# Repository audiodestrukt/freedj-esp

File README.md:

# freedj-esp

DJ decks on ESP32 (formerly esp32-mediaplayer). Two firmwares live here:

- **The ESP32-P4 deck** in [`p4/deck`](p4/deck/README.md): a small CDJ/XDJ-style player
  with Pro DJ Link sync, rekordbox analysis, a touch screen and a 3D-printed enclosure design.
- **The ESP32-A1S timecode-vinyl player** (this directory): described below.

The A1S firmware is an ESP32-A1S media player aimed at eventually driving a portable DJ turntable
with Serato timecode vinyl control. Plays MP3/WAV from an SD card with
variable-speed playback (pitched or pitch-preserving), OLED file browser, and
cue points.

The P4 deck shares the deck events, DJ2Go decoder and WSOLA with this firmware.

The long-term target is a self-contained turntable deck: drop a control
record on the platter and the ESP32 decodes position and speed from the
timecode, playing the selected MP3 in perfect sync with the vinyl.

## Status

Scaffold-complete. Untested on hardware — awaiting a board.

| Area | State |
| --- | --- |
| PlatformIO project (ES8388 + AC101 build envs) | Done |
| MP3 + WAV playback from SD | Done |
| SSD1306 OLED browser + now-playing UI | Done |
| Rotary encoder + 3 buttons, long-press state machine | Done |
| Pitched variable speed (resampler) | Done |
| Keylock variable speed (WSOLA) | Done (host-validated via SDL player) |
| Cue points (byte-level seek) | Done (glitches on MP3 mid-frame) |
| Timecode: speed + direction | Done (validated on Serato CD) |
| Timecode: bit decode + absolute position | Done host-side; ESP32 LUT pending |
| Codec RX (line-in) path for timecode input | TODO |
| Host simulation (SDL GUI + DSP harnesses) | Done |

## Hardware

- **Board:** AI-Thinker ESP32-A1S Audio Kit. Two revisions ship with
  different codecs (ES8388 or AC101) with no PCB silkscreen difference —
  check the IC marking near the 3.5 mm jacks. Both are supported by
  separate PlatformIO environments.
- **SD card:** inserted in the A1S slot (uses SD-MMC 1-bit mode).
- **Display:** 128×64 SSD1306 OLED over I²C. Shares the codec's I²C bus
  (SDA = GPIO 33, SCL = GPIO 32). No conflict: SSD1306 lives at `0x3C`,
  ES8388 at `0x10`, AC101 at `0x1A`.
- **Input:** 1 rotary encoder with push switch + 3 push buttons.
  Internal pull-ups are used; wire buttons to GND.

### Pin assignments

Default pin mapping (see `include/config.h` to adjust):

| Function | GPIO |
| --- | --- |
| Encoder A | 19 |
| Encoder B | 23 |
| Encoder switch | 18 |
| Button: Play/Pause | 5 |
| Button: Back | 21 |
| Button: Cue | 22 |
| OLED SDA (shared with codec) | 33 |
| OLED SCL (shared with codec) | 32 |

These are all pins exposed on the A1S J1/J2 expansion headers. The codec,
I²S bus, and SD card use their own dedicated pins and should be left alone.

## Building

Install [PlatformIO](https://platformio.org/) (CLI or the VS Code
extension). Then pick the build environment that matches your A1S codec:

```bash
# ES8388 variant (more common on recent A1S boards)
pio run -e esp32-a1s-es8388 -t upload

# AC101 variant
pio run -e esp32-a1s-ac101 -t upload
```

Serial monitor:

```bash
pio device monitor -b 115200
```

Wrong environment? Audio will be silent or distorted even though the board
boots — re-flash with the other env.

## Controls

| Screen | Input | Action |
| --- | --- | --- |
| Browser | Encoder CW/CCW | Scroll file list |
| Browser | Encoder press / Play | Play selected file |
| Playing | Encoder CW/CCW | Nudge speed ±0.02× |
| Playing | Encoder short-press | Snap speed to 1.0× |
| Playing | Encoder long-press (400 ms) | Toggle keylock / pitched |
| Playing | Play | Pause / resume |
| Playing | Back | Stop and return to browser |
| Playing | Cue short-press | Jump to cue point (or restart if no cue) |
| Playing | Cue long-press | Set cue point at current position |

### Serial interface

For bringing up an A1S without an OLED wired: the firmware mirrors the
UI to the 115200-baud serial console and accepts single-char keys.
`pio device monitor -b 115200`, then:

| Screen | Key | Action |
| --- | --- | --- |
| Browser | `w` / `s` | Scroll up / down |
| Browser | Enter | Play selected |
| Playing | `+` / `-` | Nudge speed ±0.02× |
| Playing | `[` / `]` | Nudge speed ±0.10× (coarse) |
| Playing | `=` | Snap speed to 1.0× |
| Playing | `K` | Toggle keylock / pitched |
| Playing | `p` or space | Pause / resume |
| Playing | `b` | Back to browser |
| Playing | `c` | Jump to cue |
| Playing | `C` | Set cue at current position |
| Any | `t` | Arm / disarm timecode input |
| Any | `?` | Print key help |

## How it works

### Audio pipeline

```
SD file ─► StreamCopy ─► EncodedAudioStream(MP3 or WAV)
                                    │
                                    ▼
                         ┌──── ResampleStream ────┐    (Pitched mode)
                         │                        │
                         └──── WsolaStream   ─────┘    (Keylock mode)
                                    │
                                    ▼
                           AudioBoardStream (I²S + codec)
```

The player wires both speed stages in parallel and routes the copier
to whichever matches the selected mode. Only the active stage drains input.

### WSOLA (Waveform-Similarity Overlap-Add)

Time-domain pitch-preserving stretching. For each output chunk:

1. Extract a 1024-sample analysis window from the input, starting near
   `analysisPos += HOP_SYN × speed`.
2. Search ±128 samples around that position for the window whose leading
   samples best match the natural continuation of the previous window
   (AMDF similarity on mono-summed input — cheaper than cross-correlation).
3. Hann-window the chosen frame and overlap-add onto the running output
   (75 % overlap).

Parameters (44.1 kHz): `FRAME_N = 1024`, `HOP_SYN = 256`, `SEARCH = 128`.
See `src/wsola.cpp`.

### CPU budget (unmeasured)

Rough estimates on a 240 MHz ESP32, everything running on core 1
(Arduino's main loop); core 0 is idle since we don't use WiFi/BT.

| Path                  | Est. one-core utilization |
| --------------------- | ------------------------- |
| Pitched mode          | ~20–30% (MP3 decode + DMA I²S) |
| Keylock mode          | ~35–50% (+ WSOLA: AMDF search dominates) |
| Timecode armed        | small — ZC + LFSR, a few % |

WSOLA's cost is dominated by the AMDF search: `FRAME_N × 2·SEARCH`
abs-diffs per `HOP_SYN` output samples on a mono-summed input, roughly
1K ops per output sample. Not measured on hardware yet — wrap a probe
around `player::loopTick()` with `esp_timer_get_time()` when we want a
real number.

### Timecode decoder

Implements Serato Control Vinyl and Serato Control CD decoding — speed,
direction, and absolute position on the record/CD. Source:
`src/timecode.{h,cpp}`.

```
int16 stereo in ─► per-channel ZC with hysteresis + DC-tracking zero
                   │                              │
                   ▼                              ▼
           direction (primary vs          period between primary ZCs
            secondary polarity at ZC)     → carrier speed (EMA-smoothed)
                   │                              │
                   ▼                              │
         bit sample at secondary ZC               │
         (|primary| vs running ref_level → 1/0)   │
                   │                              │
                   ▼                              │
         20-bit shift register + LFSR predictor   │
         (VALID_BITS = 24 consecutive matches     │
          before position is trusted)             │
                   │                              │
                   ▼                              │
         LUT lookup ► absolute cycle position ◄───┘
```

**Supported formats** (constants are published reverse-engineered facts
about Serato's commercial products):

| Format | Carrier | Bits | Seed | Taps | Length |
| --- | --- | --- | --- | --- | --- |
| Serato Control Vinyl 2nd ed. | 1 kHz | 20 | `0x59017` | `0x361e4` | 712 000 cycles |
| Serato Control CD | 1 kHz | 20 | `0xd8b40` | `0x34d54` | 950 000 cycles |

Resolution is one decoded cycle per millisecond of reference playback
(1 kHz carrier). With `VALID_BITS = 24`, lock takes ~25 ms of correct
bits plus ref-level EMA settling — measured at ~160 ms cold-start on a
clean capture.

**Host validation.** A reference 980 s capture of the Serato CD in the
repo (`timecode.wav`, not committed — supply your own) is decoded by
`native/timecode_analyze`; seek-offset positions decode linearly across
the usable range of the disc with perfect inter-sample consistency. A
constant LFSR-to-disc offset (≈2604 cycles for this pressing) is
absorbed when the player anchors position at playback start.

**ESP32 caveat.** The position LUT is host-only today —
`std::unordered_map` with ~30 MB footprint for `serato_cd`. The ESP32
path returns `position() = -1` while still producing correct speed and
direction. A PSRAM-resident compact LUT is the remaining work to ship
position decode on hardware.

**Licensing.** This is a clean-room implementation of the algorithm
described by [xwax](https://xwax.org/) — no xwax source was copied.
xwax is GPL-3; its code cannot be merged into this project without
relicensing. The format constants above are facts about Serato's
products, not copyrightable expression, and appear in multiple
independent open-source DVS implementations.

## Host simulation and testing

The firmware is structured so the DSP modules (`src/wsola.{h,cpp}` and
`src/timecode.{h,cpp}`) build cleanly against a host toolchain via
`-DWSOLA_NATIVE -DTIMECODE_NATIVE`, letting us validate them without
hardware. Host artifacts live under `native/` (SDL + gcc) and `sim/`
(Wokwi headless simulation).

### native/ — gcc + SDL harnesses

```
make -C native            # builds everything
```

Produces four binaries:

| Binary | Purpose |
| --- | --- |
| `wsola_play <file.wav> [speed]` | Feed a WAV through `Wsola`, emit raw PCM to stdout. Pipe to `aplay -f S16_LE -c 2 -r 44100`. |
| `mediaplayer ./media` | SDL 640×360 window reproducing the ESP32 UI (browser + playing screen) against a real WAV directory. Keyboard stands in for encoder/buttons. |
| `timecode_test` | Synthetic stereo-carrier smoke test — exercises ZC, direction, and period estimation across 500/1000/1500/2000 Hz. |
| `timecode_analyze <file.wav> [hop_ms]` | Stream mode: print speed/locked/position time series. |
| `timecode_analyze <file.wav> seek <off_s> [dur_s]` | Seek mode: decode a window, compare decoded position to ground-truth cycle offset. |
| `vinyl_demo <tc.wav> <music.wav> <tc_speed>` | End-to-end loop: resamples TC at `tc_speed` (simulating platter spin), decodes it, drives WSOLA on the music — music plays keylocked at the decoded speed. Stereo PCM to stdout. |

The same `src/wsola.cpp` and `src/timecode.cpp` that ship to the ESP32
are compiled here — only Arduino and AudioTools includes are guarded
out. One source of truth for DSP correctness.

### sim/ — Wokwi headless simulation

`sim/diagram.json` + `sim/wokwi.toml` + `sim/scenario.test.yaml` drive
the Wokwi CLI against the `esp32-sim` PlatformIO environment
(`src/main_sim.cpp` replaces `main.cpp`, strips audio deps, keeps UI +
controls). Serial assertions verify the state machine.

```
make -C native run_wokwi    # builds esp32-sim firmware and runs scenario
```

Needs `WOKWI_CLI_TOKEN` in `./.env` (gitignored); the target bails with
a clear error if it's missing.

This validates the non-audio half of the firmware (OLED rendering,
encoder/button handling, state transitions). Wokwi does **not**
simulate the ESP32 I²S peripheral — `mediaplayer` in `native/` is where
audio behaviour is exercised.

Common run targets (all under `make -C native`):

| Target | What it does |
| --- | --- |
| `run_sim` | Launch the SDL mediaplayer against `native/media/` |
| `run_wokwi` | Build esp32-sim firmware and run the Wokwi scenario |
| `run_play WAV=x.wav SPEED=1.25` | Pipe `wsola_play` output to `aplay` |
| `run_tc` | Run the synthetic-carrier timecode smoke test |
| `run_tc_wav TC_WAV=path.wav` | Stream a real capture through `timecode_analyze` |
| `run_vinyl_demo DEMO_SPEED=1.25 MUSIC=path.wav` | TC drives music playback (keylocked) via WSOLA — piped to aplay |

## References / inspiration

- [pschatzmann/arduino-audio-tools](https://github.com/pschatzmann/arduino-audio-tools) —
  the audio framework this player is built on, especially the
  [`player-sd-audiokit`](https://github.com/pschatzmann/arduino-audio-tools/tree/main/examples/examples-player/player-sd-audiokit) example.
- [bbulkow/loudframe](https://github.com/bbulkow/loudframe) — reference for
  SD playback and variable-speed handling on the A1S.
- [xwax](https://xwax.org/) — algorithmic reference for the timecode
  decoder. Our implementation is a clean-room rewrite (GPL-3 xwax code
  is not included); the Serato format constants are reverse-engineered
  facts originally published there.
- Verhelst & Roelands, "An Overlap-Add Technique Based on Waveform
  Similarity (WSOLA) For High Quality Time-Scale Modification of Speech",
  ICASSP 1993.

## License

Copyright (c) 2026 Dan Newcome.

- **Software** (both firmwares, the simulator, tests and tools): [GPL-3.0-or-later](LICENSE).
- **Hardware** (`p4/deck/hardware`: enclosure CAD, generated STLs, renders): [CERN-OHL-S-2.0](p4/deck/hardware/LICENSE).

- **Names:** "freedj" and audiodestrukt are Dan Newcome's trademarks and aren't covered by those licences. If you ship a modified version, give it a name of your own.
- **No affiliation:** not affiliated with or endorsed by Pioneer DJ / AlphaTheta, Serato, Numark or any other brand named here. Those names are used only to describe compatibility.

See [COPYRIGHT.md](COPYRIGHT.md) for which licence covers what, the third-party code, and trademarks.

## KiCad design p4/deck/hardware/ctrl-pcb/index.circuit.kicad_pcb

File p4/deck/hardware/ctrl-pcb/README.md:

# freedj control board

One 42 × 58 mm two-layer board under CUE / PLAY. It carries:
- the two buttons and their ring LEDs,
- the pitch fader input,
- one I2C target chip that does the ADC, button debouncing and LEDs for the host.

The AS5600 jog encoder shares the same I2C bus through the board. The host is the P4 dev board, a Pi Zero or a Teensy, over a single 5-wire cable.

## The chip: CH32V003F4P6

A 32-bit RISC-V microcontroller (WCH), TSSOP-20, LCSC **C5187096**: 26,000+ in stock at JLCPCB, about $0.29.

- **One chip does it all.** It has:
  - a hardware I2C target,
  - a 10-bit ADC for the fader (oversampled in firmware for more resolution),
  - GPIO for the two buttons, debounced in firmware,
  - one pin per LED, so firmware can dim and animate them.
- **Why not fixed-function chips:** an ADC plus a GPIO expander (ADS1015 + PCA9555) would still need firmware-side debouncing, and costs more parts.
- **Why not an ATtiny 1-/2-series:** the ATtiny1616 / 1626 would do the same job, but JLCPCB had only 47–108 in stock.
- **Programming:** one wire (SWIO) from a **WCH-LinkE** (about $5), with 3V3, GND and SWIO on the bottom-side pads. ch32fun or the openwch Arduino core both build for it.

## Pins

| CH32V003 | Use | | CH32V003 | Use |
|---|---|---|---|---|
| 1 PD4 | LED CUE 1 | | 11 PC1 | SDA (I2C target) |
| 2 PD5 | LED CUE 2 | | 12 PC2 | SCL |
| 3 PD6 | LED CUE 3 | | 13 PC3 | INT to host (open drain, 10k pull-up) |
| 4 PD7 | NRST (10k pull-up) | | 14 PC4 | Fader wiper, ADC A2, 1k + 100 nF filter |
| 5 PA1 | LED PLAY 1 | | 15 PC5 | PLAY button (internal pull-up, to GND) |
| 6 PA2 | LED PLAY 2 | | 16 PC6 | CUE button |
| 7 VSS | GND | | 17 PC7 | LED CUE 4 |
| 8 PD0 | LED PLAY 3 | | 18 PD1 | SWIO (programming pad) |
| 9 VDD | 3V3 (100 nF + 10 µF) | | 19 PD2 | spare |
| 10 PC0 | LED PLAY 4 | | 20 PD3 | spare |

LEDs are driven high, with the cathode to GND:
- **PLAY:** KT-0805G green (C2297) with **100 Ω**.
- **CUE:** KT-0805Y 590 nm amber-yellow (C2296) with **470 Ω**.

That's about 3–5 mA each at 3.3 V. Both are JLCPCB basic parts. Use PWM in firmware to match their brightness.

The switches are **ZX-QC66-7.5TP**, 6 × 6 mm SMD, 7.5 mm tall (C7470157). Each is wired across its diagonal pads (1 and 4), which are switched whichever way the contacts pair up inside.

## Connectors (JST-XH, through-hole, soldered on the bottom)

| | Pin 1 | 2 | 3 | 4 | 5 |
|---|---|---|---|---|---|
| **J_HOST** (back edge) | 3V3 | GND | SDA | SCL | INT |
| **J_ENC** (right edge, AS5600) | 3V3 | GND | DIR (tied to GND) | SCL | SDA |
| **J_POT** (right edge, fader) | 3V3 (one end) | wiper | GND (other end) | | |

- **Pull-ups:** I2C has 4.7k pull-ups on this board. On the P4, use a **separate I2C bus** from the codec/touch bus.
- **AS5600:** its address (0x36) doesn't clash with the CH32V003, which will use 0x42 once its firmware exists.

## How it fits the case

The outline, the three M2.5 holes, the switch centres, the LED circle and the connector positions all come from the enclosure CAD:
1. `gen_geom.py` reads them from `../cad/machine_params.py` and `../cad/ctrlboard.py`.
2. It writes them to `lib/geom.json`.
3. `index.circuit.tsx` places from that file.

**Keep-out:** each light ring's skirt sits on r 10.8–11.8 mm around its switch centre. Only the LEDs go there, under notches in the skirt. The bosses come down onto the top face around the holes, so keep r 3 mm there clear too. `build.sh` doesn't check these keep-outs; the checks run were one-off.

## Build

```bash
npm ci                                   # tscircuit, same versions as freedj-3000
ln -s ~/.claude/skills/pcb-layout/scripts scripts
./build.sh
```

`build.sh` does the whole board:
1. Reads the anchors from the CAD.
2. Builds the tscircuit design.
3. Routes it with Freerouting and the capacity router, keeping the better result.
4. Drops dead copper islands.
5. Finishes any open connections with TraceMaker.
6. Runs the gates: KiCad DRC, the JLCPCB DFM check and the floating-pad check.
7. Writes `fab/`.

The tscircuit build reports 34 pad-clearance "errors" between the MCU's own pins. These are false: they come from its rotated pill-shaped pads, and KiCad's DRC on the exported board is clean.

## Ordering (JLCPCB)

- **PCB:** `fab/freedj-ctrl-gerbers.zip`, 2 layers, 1.6 mm.
- **Assembly, top side:**
  - Upload `fab/freedj-ctrl-bom.csv` and `fab/freedj-ctrl-cpl.csv`, which list 27 parts.
  - Check the rotations in JLCPCB's placement preview, especially U1, the LEDs and the switches. Part rotations don't always line up between KiCad and JLCPCB's library.
- **By hand:** the three JST-XH sockets, from `fab/freedj-ctrl-handsolder.csv`. Put the housings on the **bottom** side, where their outlines are on the bottom silkscreen.

## Still to do

- **Firmware for the CH32V003:** I2C register map, debouncing, fader oversampling, LED PWM and the INT line.
- **A host driver on the P4.**

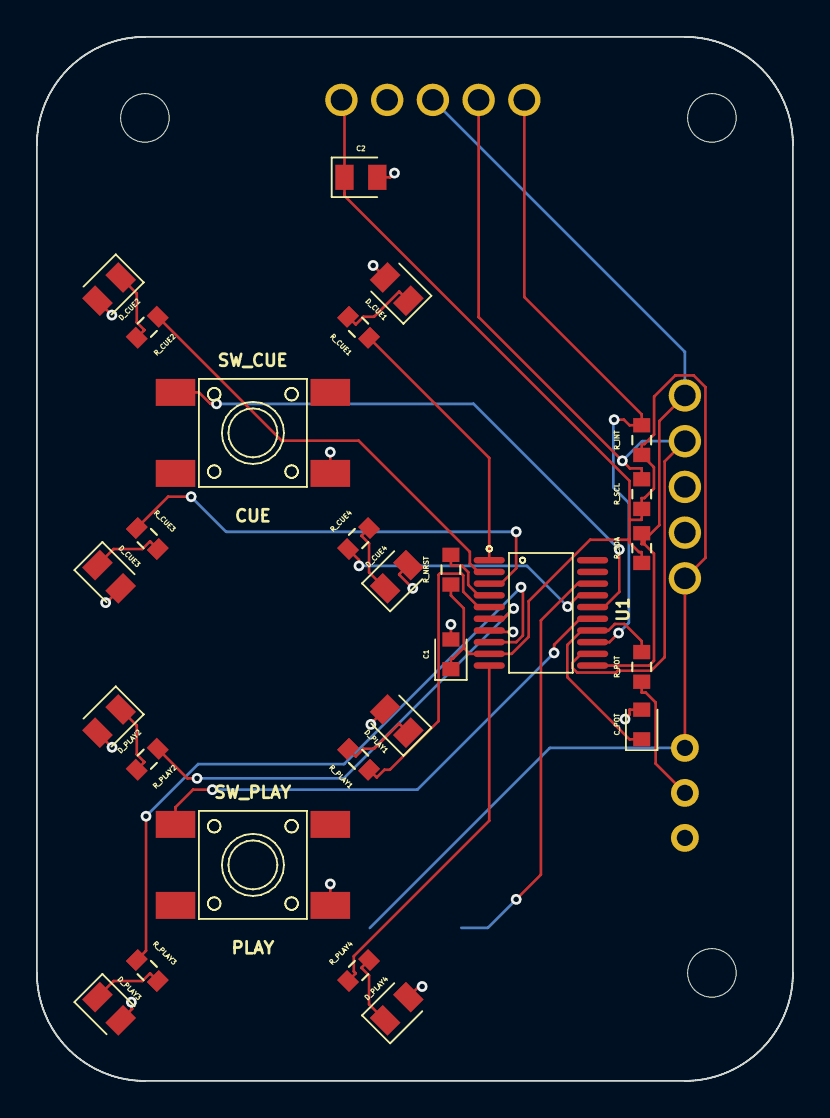
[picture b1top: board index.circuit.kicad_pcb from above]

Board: 2 copper layers, 42.0 x 58.0 mm, 33 parts (0 on the bottom side), 27 nets.

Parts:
C1: 100nF; capacitor_0603
C2: 10uF; capacitor_0805
C_POT: 100nF; capacitor_0603
D_CUE1, D_CUE2, D_CUE3, D_CUE4: LED; led_0805_color(yellow)
D_PLAY1, D_PLAY2, D_PLAY3, D_PLAY4: LED; led_0805_color(green)
J_ENC: B5B_XH_A_LF__SN_; B5B_XH_A_LF_SN
J_HOST: B5B_XH_A_LF__SN_; B5B_XH_A_LF_SN
J_POT: B3B_XH_A_LF__SN_; B3B_XH_A_LF_SN
R_CUE1, R_CUE2, R_CUE3, R_CUE4: 470Ω; resistor_res0603
R_INT: 10kΩ; resistor_res0603
R_NRST: 10kΩ; resistor_res0603
R_PLAY1, R_PLAY2, R_PLAY3, R_PLAY4: 100Ω; resistor_res0603
R_POT: 1kΩ; resistor_res0603
R_SCL: 4.7kΩ; resistor_res0603
R_SDA: 4.7kΩ; resistor_res0603
SW_CUE: ZX_QC66_7_5TP
SW_PLAY: ZX_QC66_7_5TP
TP_3V3: TP_3V3; test_point_smtpad_circle_d1.5
TP_GND: TP_GND; test_point_smtpad_circle_d1.5
TP_SWIO: TP_SWIO; test_point_smtpad_circle_d1.5
U1: CH32V003F4P6

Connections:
.R_CUE1 > .pin2 to .D_CUE1 > .anode: D_CUE1.1, R_CUE1.2
.R_CUE2 > .pin2 to .D_CUE2 > .anode: D_CUE2.1, R_CUE2.2
.R_CUE3 > .pin2 to .D_CUE3 > .anode: D_CUE3.1, R_CUE3.2
.R_CUE4 > .pin2 to .D_CUE4 > .anode: D_CUE4.1, R_CUE4.2
.R_PLAY1 > .pin2 to .D_PLAY1 > .anode: D_PLAY1.1, R_PLAY1.2
.R_PLAY2 > .pin2 to .D_PLAY2 > .anode: D_PLAY2.1, R_PLAY2.2
.R_PLAY3 > .pin2 to .D_PLAY3 > .anode: D_PLAY3.1, R_PLAY3.2
.R_PLAY4 > .pin2 to .D_PLAY4 > .anode: D_PLAY4.1, R_PLAY4.2
.U1 > .pin1 to .R_CUE1 > .pin1: R_CUE1.1, U1.1
.U1 > .pin2 to .R_CUE2 > .pin1: R_CUE2.1, U1.2
.U1 > .pin3 to .R_CUE3 > .pin1: R_CUE3.1, U1.3
.U1 > .pin5 to .R_PLAY1 > .pin1: R_PLAY1.1, U1.5
.U1 > .pin6 to .R_PLAY2 > .pin1: R_PLAY2.1, U1.6
.U1 > .pin8 to .R_PLAY3 > .pin1: R_PLAY3.1, U1.8
.U1 > .pin10 to .R_PLAY4 > .pin1: R_PLAY4.1, U1.10
.U1 > .pin17 to .R_CUE4 > .pin1: R_CUE4.1, U1.17
BTN_CUE: SW_CUE.1, U1.16
BTN_PLAY: SW_PLAY.1, U1.15
GND: C1.2, C2.2, C_POT.2, D_CUE1.2, D_CUE2.2, D_CUE3.2, D_CUE4.2, D_PLAY1.2, D_PLAY2.2, D_PLAY3.2, D_PLAY4.2, J_ENC.2, J_ENC.3, J_HOST.2, J_POT.3, SW_CUE.4, SW_PLAY.4, TP_GND.1, U1.7
INT: J_HOST.5, R_INT.2, U1.13
NRST: R_NRST.2, U1.4
POT: C_POT.1, R_POT.2, U1.14
SCL: J_ENC.4, J_HOST.4, R_SCL.2, U1.12
SDA: J_ENC.5, J_HOST.3, R_SDA.2, U1.11
SWIO: TP_SWIO.1, U1.18
V3V3: C1.1, C2.1, J_ENC.1, J_HOST.1, J_POT.1, R_INT.1, R_NRST.1, R_SCL.1, R_SDA.1, TP_3V3.1, U1.9
WIPER: J_POT.2, R_POT.1
